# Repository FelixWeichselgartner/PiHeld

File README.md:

# PiHeld

This project is the first Raspberry Pi based handheld console to include a GameBoy cartridge reader.

The PCBs are under active testing and will a working prototype should be available soon. Be a bit more patient of you want to use the PCBs ;).

## Preview

## Build guide

TODO: Here include all parts and how to build the system.

## Developer information

For Documentation check out [this](./doc/).

TODO: Here include information needed for developers.

# Further improvements (to-do list):

* Add a HDMI (or Mini-HDMI) Connector to the CM4 (on display-pcb) to give the user a Nintendo Switch like experience.
* Make a version compatible with the Raspberry Pi Zero, as it is cheaper and more commonly used.
* Make a version that fits in a GameBoy Color/Pocket shell. As those only have one pcb inside, the display and cartridge pcb could be combined to a single pcb. This would make the production part significantly easier.
* Make the USB-Charging port bidirectional. This enables users to connect e.g. a keyboard to the device (USB OTG).
* Update the software to enable users to interface with GameBoy Color cartridges.
* Theoretically GameBoy Advance cartridges could also be used with the system. Maybe some minor hardware modifications would be needed for this. Also the GBA cartridges do not fit in the GB/GBC/GBP cartridge slot.
* Make a custom OS-Image that already features the needed modifications for the hardware.
* Cartridge-pcb version with MCP23S17, as SPI is a lot faster than I²C.

## License

This project is completely open source, as we want everybody to be able to build their own PiHeld. Check out the `License.md` file to get further information on licensing.

## Split-off projects

* https://github.com/FelixWeichselgartner/Arduino_Logic_Analyzer
* https://github.com/FelixWeichselgartner/Adafruit_PowerBoost_SaveShutdown
* https://github.com/FelixWeichselgartner/RPi-I2C-LevelShifter
* https://github.com/FelixWeichselgartner/rpi-mcp23017

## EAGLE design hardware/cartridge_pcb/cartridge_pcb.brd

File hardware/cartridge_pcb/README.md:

# Cartridge PCB

The cartridge pcb includes the following:
* Connectors
    * Micro USB Connector
    * SD-Card Connector
* Power Management
    * Power-Switch
    * RGB-Led (charging/low-battery/fully-charged)
    * LiPo connector
    * LiPo-BoostUp connector
* Cartridge dumper
    * 2x MCP23017 for cartridge
* Save shutdown circuit
* ADC for battery percentage
* optional IC for fast level shifting

### Schematic

### Layout

### Gerber Preview

### Breakout board for cartridge adapter to adjust height for gameboy shell

## License

Creative Commons Attribution-ShareAlike 4.0 International License (see `LICENSE` file).

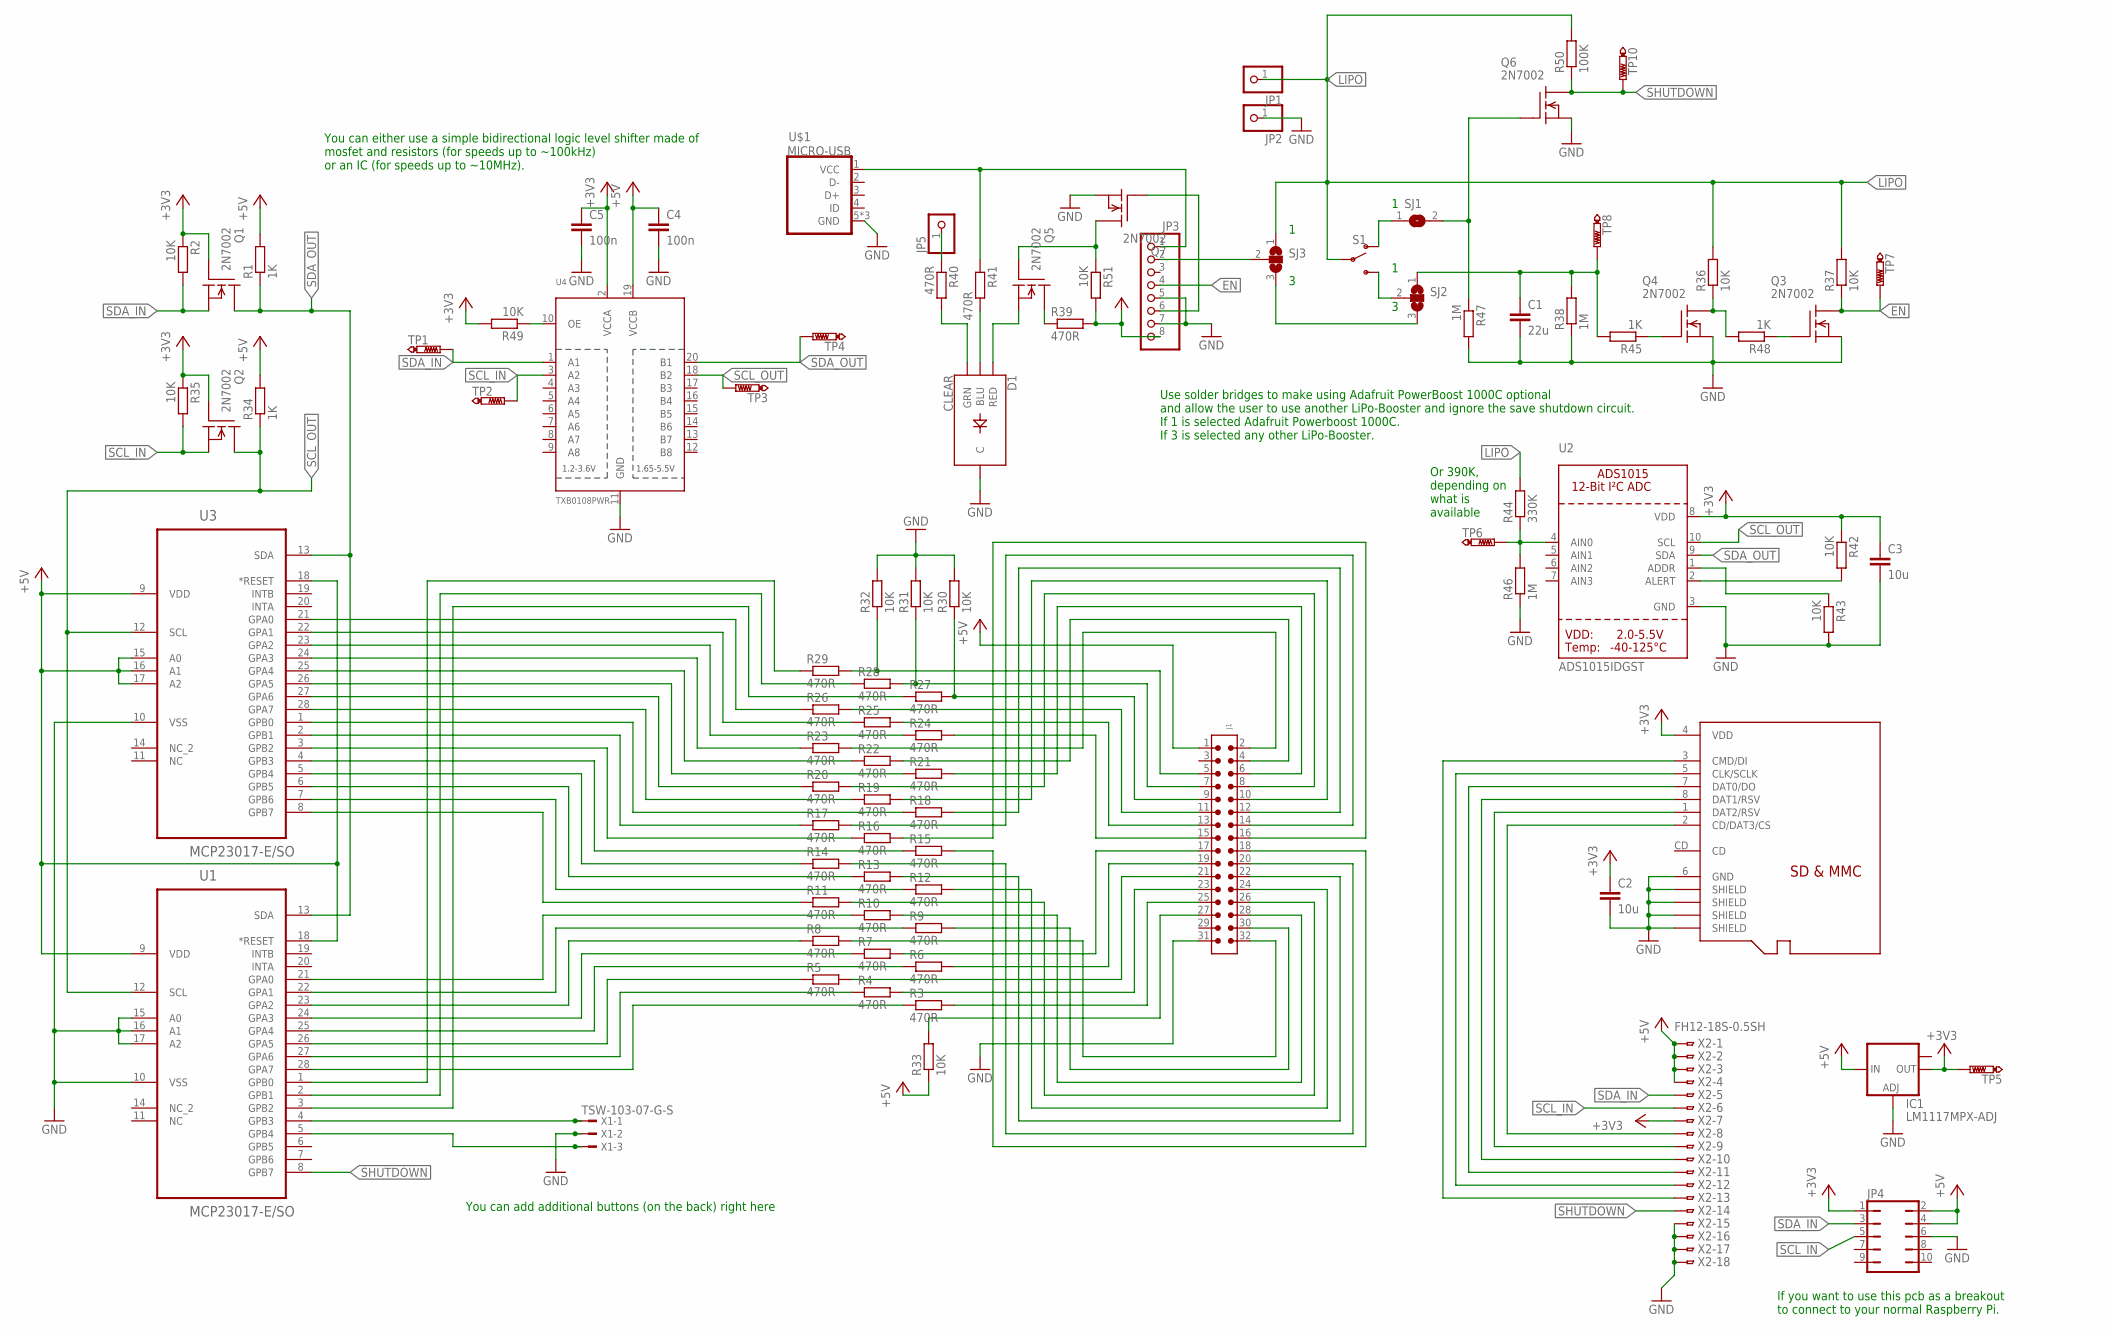
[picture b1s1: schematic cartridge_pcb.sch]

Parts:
C1: 22u; C0805
C2, C3: 10u; C0805
C4, C5: 100n; C0805
D1: CLEAR; LED-RGB-THRU
IC1: LM1117MPX-ADJ; SOT223
J1: 6130XX21121_61303221121; 61303221121
JP1, JP2, JP5: PINHD-1X1; 1X01
JP3: HEADER-1X8ROUND; 1X08_ROUND
JP4: JP5Q
Q1, Q2, Q3, Q4, Q5, Q6, Q7: 2N7002; SOT23
R1, R34, R45, R48: 1K; R0805
R2, R30, R31, R32, R33, R35, R36, R37, R42, R43, R49, R51: 10K; R0805
R3, R4, R5, R6, R7, R8, R9, R10, R11, R12, R13, R14, R15, R16, R17, R18, R19, R20, R21, R22, R23, R24, R25, R26, R27, R28, R29, R39, R40, R41: 470R; R0805
R38, R46, R47: 1M; R0805
R44: 330K; R0805
R50: 100K; R0805
S1: SWITCH-SPDT-PTH-8.6X4.3MM-LOCK; SWITCH_SPDT_8.6X4.3MM_LOCK
SJ1: SJ
SJ2, SJ3: SJ2W; SJ_2
TP1, TP2, TP3, TP4, TP5, TP6, TP7, TP8, TP10: PTR1TP10R; TP10R
U1, U3: MCP23017-E/SO; SOIC127P1032X265-28N
U2: ADS1015IDGST; MSOP10
U4: TXB0108PWR; TSSOP20
U$1: MICRO-USB
U$2: MICROSD; C12075
X1: TSW-103-07-G-S; TSW-103-XX-G-S
X2: FH12-18S-0.5SH

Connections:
+3V3: C2.1, C3.1, C5.1, IC1.2 (OUT), JP4.1, Q1.1 (G), Q2.1 (G), R2.1, R35.1, R42.1, R49.2, TP5.TP, U2.8 (VDD), U4.2 (VCCA), U$2.4 (VDD), X2.7
+5V: C4.1, IC1.3 (IN), J1.1, JP3.8, JP4.2, JP4.4, R1.2, R33.1, R34.2, R39.2, R51.2, U1.9 (VDD), U1.18 (*RESET), U3.9 (VDD), U3.15 (A0), U3.16 (A1), U3.17 (A2), U3.18 (*RESET), U4.19 (VCCB), X2.1, X2.2, X2.3, X2.4
EN: JP3.4, Q3.3 (D), R37.1, TP7.TP
GND: C1.2, C2.2, C3.2, C4.2, C5.2, D1.2 (C), IC1.1 (ADJ), J1.31, JP2.1, JP3.5, JP3.7, JP4.6, Q3.2 (S), Q4.2 (S), Q6.2 (S), Q7.2 (S), R30.2, R31.2, R32.2, R38.1, R43.2, R46.1, R47.2, U1.10 (VSS), U1.15 (A0), U1.16 (A1), U1.17 (A2), U2.3 (GND), U3.10 (VSS), U4.11 (GND), U$1.5 (GND), U$1.GND1 (GND), U$1.GND2 (GND), U$2.6 (GND), U$2.GND@1 (SHIELD), U$2.GND@2 (SHIELD), U$2.GND@3 (SHIELD), U$2.GND@4 (SHIELD), X1.2, X2.15, X2.16, X2.17, X2.18
LIPO: JP1.1, R36.2, R37.2, R44.2, R50.2, S1.2, SJ3.1
unnamed: R12.1, U3.7 (GPB6)
unnamed: R11.1, U3.8 (GPB7)
unnamed: R10.1, U1.21 (GPA0)
unnamed: R3.1, U1.28 (GPA7)
unnamed: R13.1, U3.6 (GPB5)
unnamed: R14.1, U3.5 (GPB4)
unnamed: R15.1, U3.4 (GPB3)
unnamed: R16.1, U3.3 (GPB2)
unnamed: R17.1, U3.2 (GPB1)
unnamed: R18.1, U3.1 (GPB0)
unnamed: R19.1, U3.28 (GPA7)
unnamed: R20.1, U3.27 (GPA6)
unnamed: R21.1, U3.26 (GPA5)
unnamed: R22.1, U3.25 (GPA4)
unnamed: R23.1, U3.24 (GPA3)
unnamed: R24.1, U3.23 (GPA2)
unnamed: R25.1, U3.22 (GPA1)
unnamed: R26.1, U3.21 (GPA0)
unnamed: R9.1, U1.22 (GPA1)
unnamed: R8.1, U1.23 (GPA2)
unnamed: R7.1, U1.24 (GPA3)
unnamed: R6.1, U1.25 (GPA4)
unnamed: R5.1, U1.26 (GPA5)
unnamed: R4.1, U1.27 (GPA6)
unnamed: J1.25, R3.2
unnamed: J1.23, R4.2
unnamed: J1.19, R6.2
unnamed: J1.21, R5.2
unnamed: J1.32, R8.2
unnamed: J1.30, R9.2
unnamed: J1.28, R10.2
unnamed: J1.26, R11.2
unnamed: J1.24, R12.2
unnamed: J1.22, R13.2
unnamed: J1.20, R14.2
unnamed: J1.18, R15.2
unnamed: J1.16, R16.2
unnamed: J1.14, R17.2
unnamed: J1.12, R18.2
unnamed: J1.10, R19.2
unnamed: J1.8, R20.2
unnamed: J1.6, R21.2
unnamed: J1.11, R26.2
unnamed: J1.13, R25.2
unnamed: J1.15, R24.2
unnamed: Q5.1 (G), Q7.3 (D), R51.1
unnamed: J1.17, R7.2
unnamed: J1.9, R27.2, R30.1
unnamed: J1.2, R23.2
unnamed: J1.5, R29.2, R32.1
unnamed: J1.27, R33.2
unnamed: R44.1, R46.2, TP6.TP, U2.4 (AIN0)
unnamed: R43.1, U2.1 (ADDR)
unnamed: U$2.7 (DAT0/DO), X2.11
unnamed: J1.4, R22.2
unnamed: JP3.6, Q7.1 (G)
unnamed: R27.1, U1.3 (GPB2)
unnamed: R28.1, U1.2 (GPB1)
unnamed: R29.1, U1.1 (GPB0)
unnamed: U$2.8 (DAT1/RSV), X2.10
unnamed: U$2.1 (DAT2/RSV), X2.9
unnamed: Q4.3 (D), R36.1, R48.2
unnamed: JP5.1, R40.1
unnamed: U$2.2 (CD/DAT3/CS), X2.8
unnamed: C1.1, R38.2, R45.2, SJ2.1, TP8.TP
unnamed: U$2.5 (CLK/SCLK), X2.12
unnamed: U$2.3 (CMD/DI), X2.13
unnamed: Q5.3 (D), R39.1
unnamed: J1.7, R28.2, R31.1
unnamed: D1.4 (BLU), R41.2
unnamed: D1.3 (GRN), R40.2
unnamed: D1.1 (RED), Q5.2 (S)
unnamed: Q3.1 (G), R48.1
unnamed: R42.2, U2.2 (ALERT)
unnamed: Q4.1 (G), R45.1
unnamed: S1.3 (S), SJ2.2
unnamed: S1.1 (O), SJ1.1
unnamed: JP3.2, SJ3.2
unnamed: SJ2.3, SJ3.3
unnamed: JP3.1, R41.1, U$1.1 (VCC)
unnamed: R49.1, U4.10 (OE)
unnamed: U1.4 (GPB3), X1.1
unnamed: U1.5 (GPB4), X1.3
SCL_IN: JP4.5, Q2.2 (S), R35.2, TP2.TP, U4.3 (A2), X2.6
SCL_OUT: Q2.3 (D), R34.1, TP3.TP, U1.12 (SCL), U2.10 (SCL), U3.12 (SCL), U4.18 (B2)
SDA_IN: JP4.3, Q1.2 (S), R2.2, TP1.TP, U4.1 (A1), X2.5
SDA_OUT: Q1.3 (D), R1.1, TP4.TP, U1.13 (SDA), U2.9 (SDA), U3.13 (SDA), U4.20 (B1)
SHUTDOWN: Q6.3 (D), R50.1, TP10.TP, U1.8 (GPB7), X2.14
SHUTDOWN_OLD: Q6.1 (G), R47.1, SJ1.2

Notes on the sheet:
Use solder bridges to make using Adafruit PowerBoost 1000C optional and allow the user to use another LiPo-Booster and ignore the save shutdown circuit. If 1 is selected Adafruit Powerboost 1000C. If 3 is selected any other LiPo-Booster.
You can either use a simple bidirectional logic level shifter made of mosfet and resistors (for speeds up to ~100kHz) or an IC (for speeds up to ~10MHz).
You can add additional buttons (on the back) right here
If you want to use this pcb as a breakout to connect to your normal Raspberry Pi.
Or 390K, depending on what is available

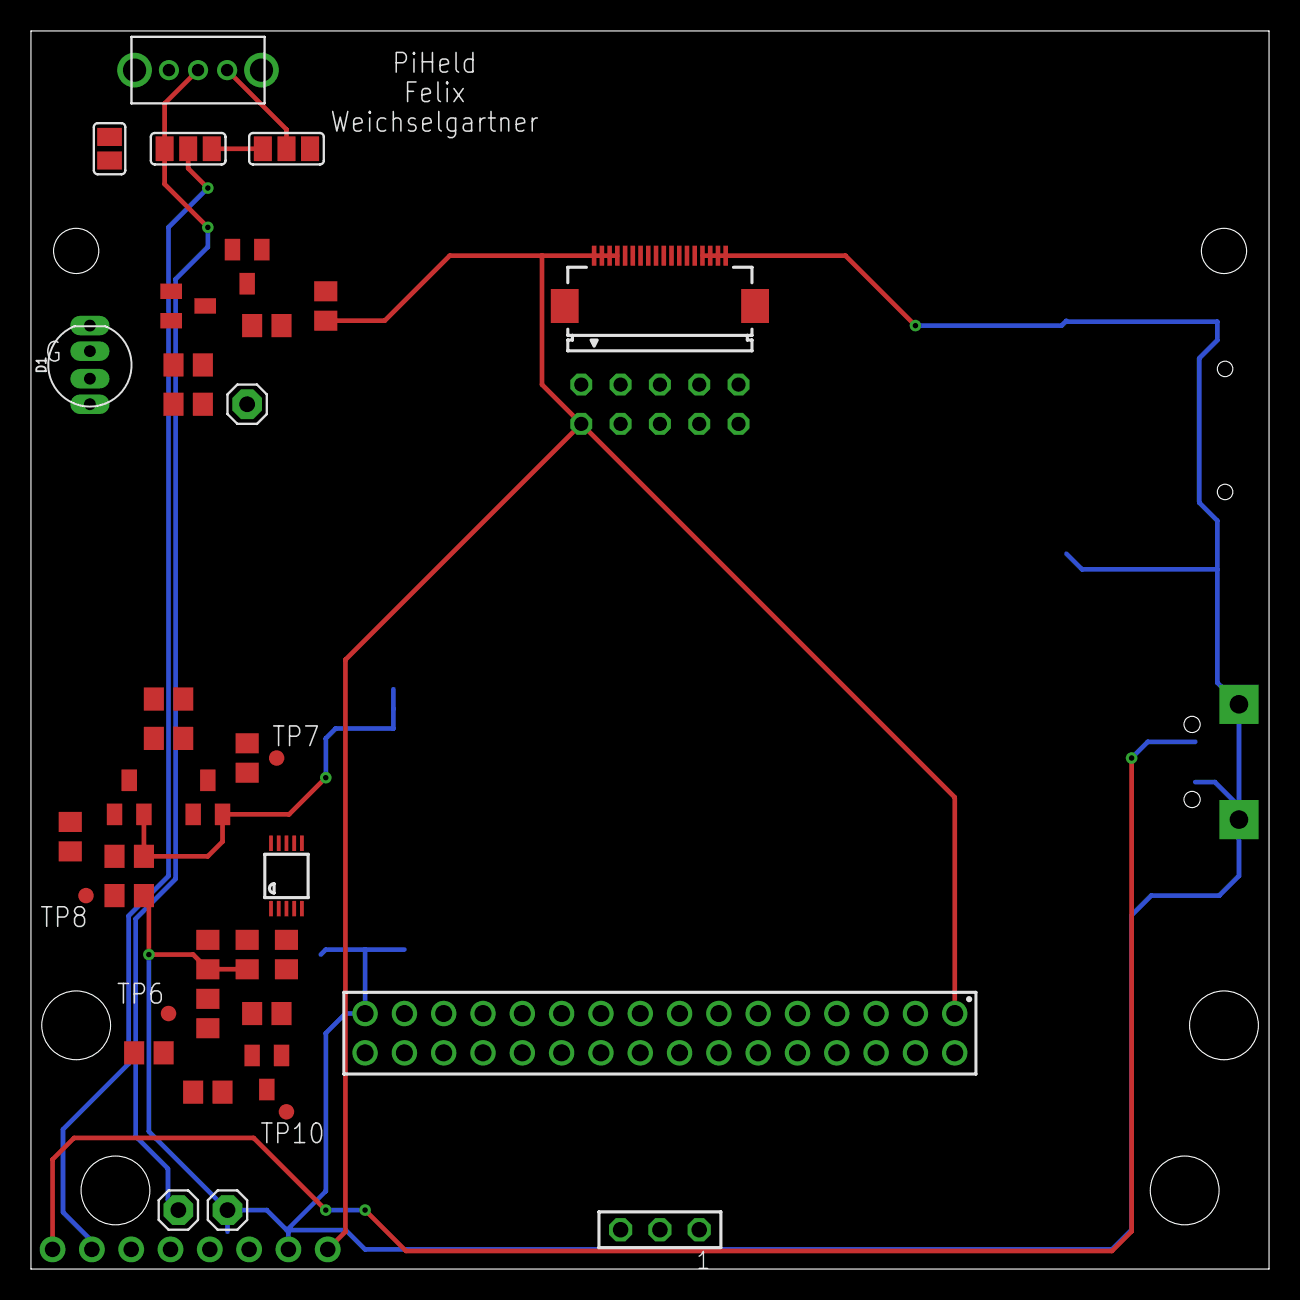
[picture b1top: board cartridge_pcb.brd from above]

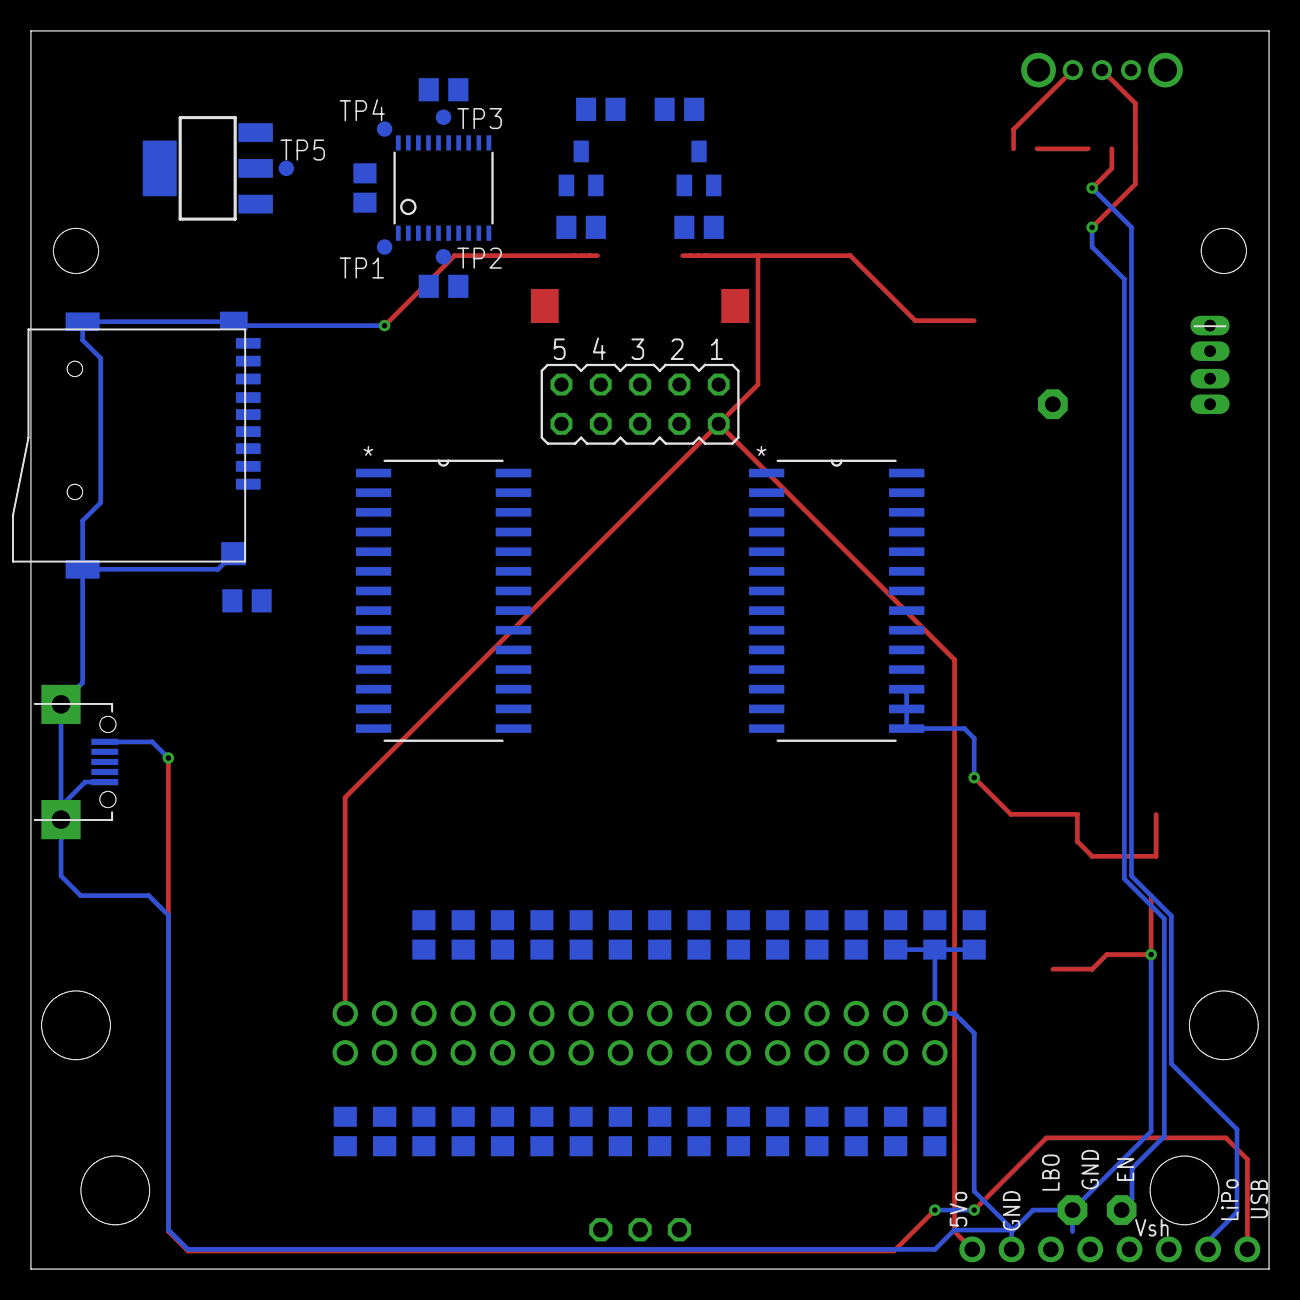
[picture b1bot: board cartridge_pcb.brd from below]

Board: 2 copper layers, 80.0 x 80.0 mm, 92 parts (53 on the bottom side), 94 nets.

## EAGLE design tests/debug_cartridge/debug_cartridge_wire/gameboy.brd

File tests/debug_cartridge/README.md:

# Debug Cartridge

 Cartridge used to debug the cartridge-pcb. Further, it can also be used to emulate a cartridge.
 
 Based on https://github.com/Xyl2k/Gameboy-Color-Cartridge with License (Unlicense) https://github.com/Xyl2k/Gameboy-Color-Cartridge/blob/master/LICENSE

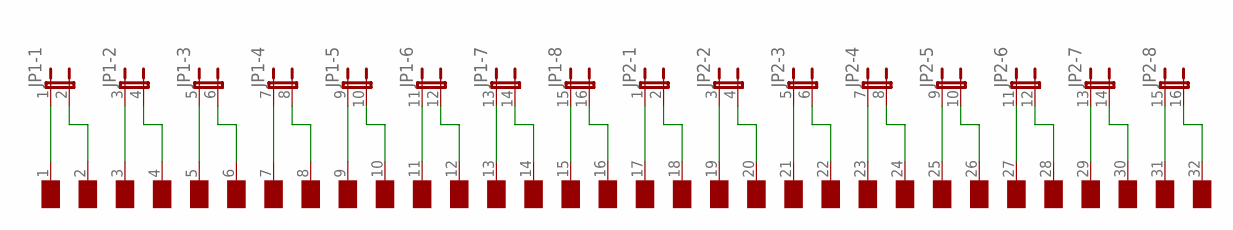
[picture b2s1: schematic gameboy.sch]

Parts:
JP1, JP2: JP8QE; JP8Q
U$1: CONNECTOR

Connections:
unnamed: JP1.1, U$1.1 (VDD)
unnamed: JP1.2, U$1.2 (NC)
unnamed: JP1.3 (1), U$1.3 (/WR)
unnamed: JP1.4 (2), U$1.4 (/RD)
unnamed: JP1.5 (1), U$1.5 (/RCS)
unnamed: JP1.6 (2), U$1.6 (A0)
unnamed: JP1.7 (1), U$1.7 (A1)
unnamed: JP1.8 (2), U$1.8 (A2)
unnamed: JP1.9 (1), U$1.9 (A3)
unnamed: JP1.10 (2), U$1.10 (A4)
unnamed: JP1.11 (1), U$1.11 (A5)
unnamed: JP1.12 (2), U$1.12 (A6)
unnamed: JP1.13 (1), U$1.13 (A7)
unnamed: JP1.14 (2), U$1.14 (A8)
unnamed: JP1.15 (1), U$1.15 (A9)
unnamed: JP1.16 (2), U$1.16 (A10)
unnamed: JP2.1, U$1.17 (A11)
unnamed: JP2.2, U$1.18 (A12)
unnamed: JP2.3 (1), U$1.19 (A13)
unnamed: JP2.4 (2), U$1.20 (A14)
unnamed: JP2.5 (1), U$1.21 (A15)
unnamed: JP2.6 (2), U$1.22 (D0)
unnamed: JP2.7 (1), U$1.23 (D1)
unnamed: JP2.8 (2), U$1.24 (D2)
unnamed: JP2.9 (1), U$1.25 (D3)
unnamed: JP2.10 (2), U$1.26 (D4)
unnamed: JP2.11 (1), U$1.27 (D5)
unnamed: JP2.12 (2), U$1.28 (D6)
unnamed: JP2.13 (1), U$1.29 (D7)
unnamed: JP2.14 (2), U$1.30 (/RS)
unnamed: JP2.15 (1), U$1.31 (VIN)
unnamed: JP2.16 (2), U$1.32 (GND)

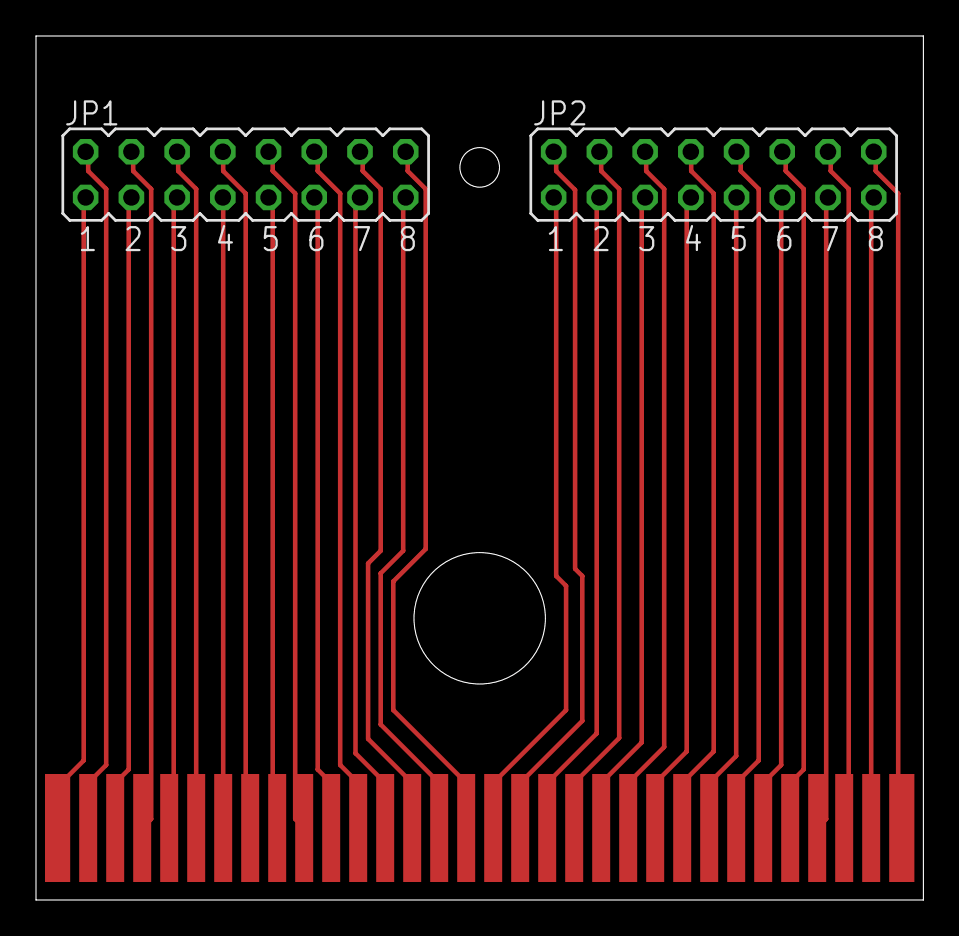
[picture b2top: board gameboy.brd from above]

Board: 2 copper layers, 49.3 x 48.0 mm, 3 parts (0 on the bottom side), 32 nets.

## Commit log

2021-07-02 initial commit with cartridge pcb
2021-07-02 typo; webhook not working
2021-07-02 fix more typos
2021-08-29 fix some issues of the cartridge pcb
2021-10-05 added second project report
2021-10-11 fix more errors in cartridge pcb which were found while testing the cartridge reader
2021-10-17 400kHz rom dumping working
2021-11-07 LiPo ADC management
2021-12-11 adjusted everything to work for debugging cpcb3
2021-12-12 more debugging tools
2021-12-30 fix typo
2022-02-01 labeled debug cartridge; updated schem/layout image of last revision pcbs
2022-02-02 integrated own mcp23017 library version instead of wiring pi
2022-02-03 filename validation; code cleanup
2022-02-03 fixed error in cpcb
2022-04-03 fixed typo

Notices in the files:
parts and their libraries:
SparkFun-Switches: Licensing: Creative Commons ShareAlike 4.0 International - https://creativecommons.org/licenses/by-sa/4.0
microbuilder: This work is placed in the public domain, and may be freely used for commercial and non-commercial work with the following conditions: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
